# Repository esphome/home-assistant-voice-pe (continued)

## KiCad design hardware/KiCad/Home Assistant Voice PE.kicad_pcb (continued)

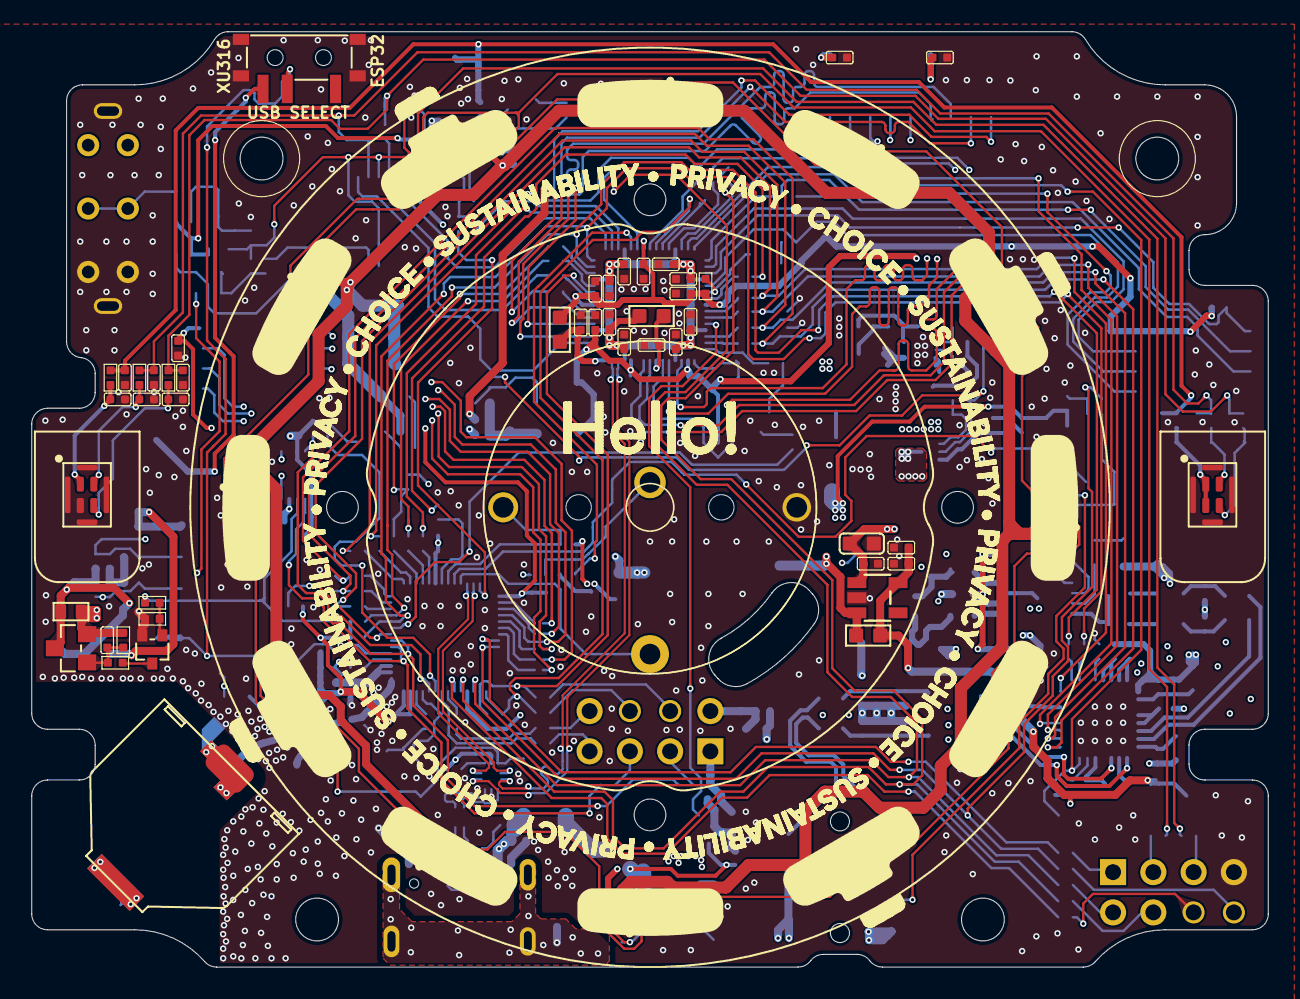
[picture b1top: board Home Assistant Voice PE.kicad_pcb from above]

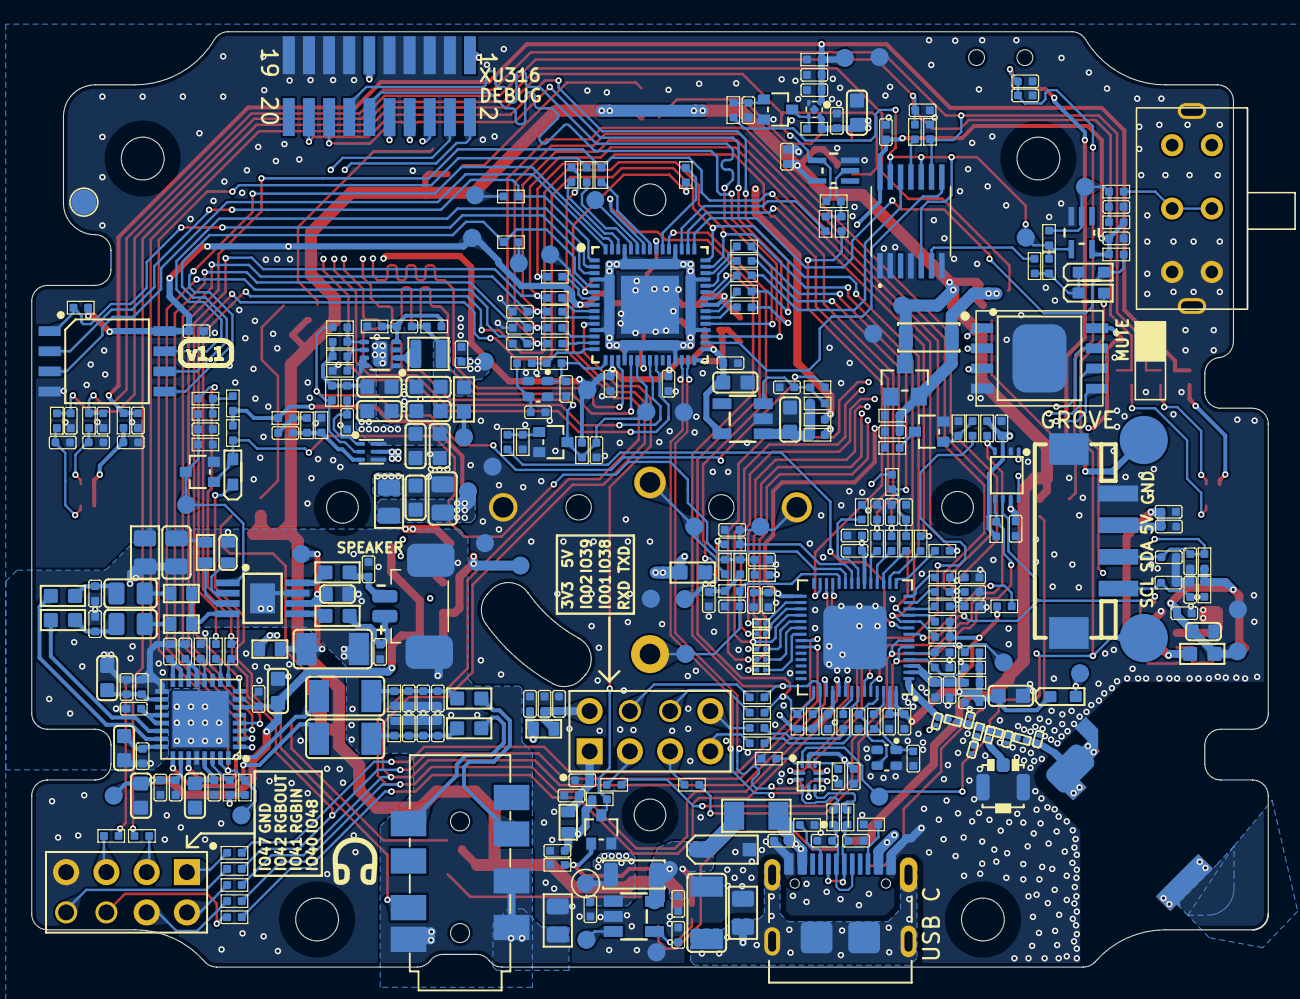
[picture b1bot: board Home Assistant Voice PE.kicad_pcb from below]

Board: 4 copper layers, 78.0 x 59.0 mm, 438 parts (365 on the bottom side), 239 nets.

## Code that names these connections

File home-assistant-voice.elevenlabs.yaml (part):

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
i2c:
  - id: internal_i2c
    sda: GPIO5
    scl: GPIO6
    frequency: 400kHz

psram:
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voice_kit:
  id: voice_kit_component
  i2c_id: internal_i2c
  reset_pin: GPIO4
  firmware:
    url: https://github.com/esphome/voice-kit-xmos-firmware/releases/download/v1.3.1/ffva_v1.3.1_upgrade.bin
    version: "1.3.1"
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i2s_audio:
  - id: i2s_output
    i2s_lrclk_pin:
      number: GPIO7
    i2s_bclk_pin:
      number: GPIO8

  - id: i2s_input
    i2s_lrclk_pin:
      number: GPIO14
    i2s_bclk_pin:
      number: GPIO13

microphone:
  - platform: i2s_audio
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    id: i2s_audio_speaker
    sample_rate: 48000
    i2s_mode: secondary
    i2s_dout_pin: GPIO10
    bits_per_sample: 32bit
    i2s_audio_id: i2s_output
    dac_type: external
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
power_supply:
  - id: led_power
    pin: GPIO45

select:
  - platform: template
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  - platform: gpio
    id: center_button
    pin:
      number: GPIO0
      inverted: true
    on_press:
      - script.execute: control_leds
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  - platform: gpio
    id: hardware_mute_switch
    internal: true
    pin: GPIO3
    on_press:
      # Play mute on sound only if software mute isn't enabled
      - if:
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      - delayed_on: 200ms
      - delayed_off: 200ms
    pin:
      number: GPIO17
    # When the jack is plugged in:
    #  - LED animation
    #  - Sound played
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  # Hardware LED ring. Not used because remapping needed
  - platform: esp32_rmt_led_strip
    id: leds_internal
    pin: GPIO21
    chipset: WS2812
    max_refresh_rate: 15ms
    num_leds: 12
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  - platform: rotary_encoder
    id: dial
    pin_a: GPIO16
    pin_b: GPIO18
    resolution: 2
    on_clockwise:
      - lambda: id(dial_touched) = true;
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
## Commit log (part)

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2024-10-17 move audio libraries to an external repo
2024-10-17 [nabu] move libraries to external repo (#167)
    * move audio libraries to an external repo
    * remove unnecessary imports
2024-10-19 Move setting global voice assistant to constructor (#168)
2024-10-21 Update voice_assistant.h (#169)
2024-10-21 Add beta install button (#171)
2024-10-21 Allow version to be specified and added as query param
2024-10-21 Allow version to be specified and added as query param (#173)
2024-10-21 [nabu] code cleanup with lint and clang fixes (#174)
2024-10-21 add more descriptive decoding errors
2024-10-21 [nabu] Improve error logging (#175)
    * reimplement flac decoder improvements
    * add more descriptive decoding errors
    * increase reader task stack size
    * remove unused variable
2024-10-21 add play local media file action
2024-10-21 [nabu] play local media file yaml action (#177)
    * add play local media file action
    * update todos
2024-10-22 Use remote paths for sounds (#178)
2024-10-22 Remove ACCESS POINT functionality (#179)
2024-10-24 use platformio library instead of repo
2024-10-24 [nabu] Use PlatformIO library instead of repo (#181)
    * use platformio library instead of repo
    * temporarily use branch
2024-10-24 reference dev branch (#182)
2025-02-19 use new audio output stack
2025-03-01 Expose Timer Events
2025-03-06 play preannounce media and enqueue the announcement
2025-03-06 only play preannounce url if non-empty
2025-03-20 build new firmware with ESPHome v2025.3.0
2025-03-24 set continue conversation boolean with start conversation flag
2025-03-25 bump build and min version to 2025.3.2
2025-03-27 Add Cloud Error Sound
2025-03-28 send "single_press" event
2025-03-31 bump to 25.3.3
2025-04-07 wake word stops ongoing VA session
2025-04-10 Better handle Stop word
2025-04-21 build with 2025.4.0
2025-04-30 Bump esphome/workflows from 2025.1.0 to 2025.4.0
    Bumps [esphome/workflows](https://github.com/esphome/workflows) from 2025.1.0 to 2025.4.0.
    - [Release notes](https://github.com/esphome/workflows/releases)
    - [Commits](https://github.com/esphome/workflows/compare/2025.1.0...2025.4.0)
    ---
    updated-dependencies:
    - dependency-name: esphome/workflows
2025-05-01 remove old external components - use the upstream versions
2025-05-02 don't use mic PR
2025-05-14 move read only and instructions from flash into psram on boot
2025-05-15 yamllint
2025-05-28 Modify default sensitivity
2025-06-26 Experimental PRs for testing, do not merge!
2025-06-29 bump build version and remove external components
2025-07-06 Switch to lock buttons
2025-07-14 feat: initial bridge
2025-07-14 fix: switch to testing via "run"
2025-07-14 fix: better test script
2025-07-14 fix: presigned url almost works
2025-07-15 fix: progress with HTTP reads
2025-07-15 fix: better elevenlabs compliance
2025-07-22 fix: more logging
2025-07-22 fix: switch to buffered approach
2025-07-22 fix: new test yaml
2025-07-22 fix: add resampler
2025-07-24 fix: compilation now works
2025-07-25 fix: type
2025-07-25 fix: cleanup later
2025-07-25 fix: reduce logging
2025-07-25 fix: elevenlabs conversation
2025-07-25 fix: better welcome message
2025-07-25 fix: better bitrate
2025-07-25 fix: higher performance
2025-07-26 fix: better activation sound
2025-07-26 fix: better documentation and better handling of speaker detection
2025-07-26 fix: implemented ring-buffer
2025-07-26 fix: buffer issue resolved
2025-07-26 fix: yaml should be OK
2025-07-26 fix: much better LED events
2025-07-26 fix: state bug
2025-07-26 fix: rename device name
2025-07-27 fix: remove voice kit
2025-07-27 fix: new parsing
2025-07-27 fix: compile issue
2025-07-27 fix: don't disable audio stream when wake word is detected during talking
2025-07-27 refactor: extract into separate classes
2025-07-27 fix: compile
2025-07-27 fix: signature.
2025-07-28 removes trailing space
2025-07-28 refactor: more cleanup
2025-07-28 refactor: base64 encoding is separate
2025-07-28 fix: compile error
2025-07-30 fix: jarvis no longer sounds like a chipmunk
2025-07-31 fix: work in progress for better speaker stability
2025-08-03 Added a configurable feature that uses the 'replying' led ring animation when playing externally triggered announcements. Enabled by default.
2025-08-12 Bump actions/checkout from 4.2.2 to 5.0.0
    Bumps [actions/checkout](https://github.com/actions/checkout) from 4.2.2 to 5.0.0.
    - [Release notes](https://github.com/actions/checkout/releases)
    - [Changelog](https://github.com/actions/checkout/blob/main/CHANGELOG.md)
    - [Commits](https://github.com/actions/checkout/compare/v4.2.2...v5.0.0)
    ---
    updated-dependencies:
2025-08-14 Add an option to processing audio file on thinking
2025-08-15 fix: stability improvements
2025-08-16 feat: add wake word sensitivity selector for Alexa
    FAPH on Dipco tests and values still missing
2025-08-25 Bump esphome/workflows from 2025.4.0 to 2025.8.1
    Bumps [esphome/workflows](https://github.com/esphome/workflows) from 2025.4.0 to 2025.8.1.
    - [Release notes](https://github.com/esphome/workflows/releases)
    - [Commits](https://github.com/esphome/workflows/compare/2025.4.0...2025.8.1)
    ---
    updated-dependencies:
    - dependency-name: esphome/workflows
2025-09-18 Bump actions/setup-python from 5 to 6
    Bumps [actions/setup-python](https://github.com/actions/setup-python) from 5 to 6.
    - [Release notes](https://github.com/actions/setup-python/releases)
    - [Commits](https://github.com/actions/setup-python/compare/v5...v6)
    ---
    updated-dependencies:
    - dependency-name: actions/setup-python
2025-10-01 Bump ESPHome to 2025.9.3
2025-10-02 Make some workflow strings more dynamic
2025-10-06 Bump esphome/workflows from 2025.8.1 to 2025.10.0
    Bumps [esphome/workflows](https://github.com/esphome/workflows) from 2025.8.1 to 2025.10.0.
    - [Release notes](https://github.com/esphome/workflows/releases)
    - [Commits](https://github.com/esphome/workflows/compare/2025.8.1...2025.10.0)
    ---
    updated-dependencies:
    - dependency-name: esphome/workflows
2025-11-01 adding support for openwakeword as a wake word engine. Adds a toggle in the home assistant integration section to switch between micro and openwakeword
2025-11-01 adding back comments and taking out more whitespace
2025-11-01 we love yaml
2025-11-19 Build with ESPHome 2025.11.0
2025-12-03 Bump actions/checkout from 5.0.0 to 6.0.1
    Bumps [actions/checkout](https://github.com/actions/checkout) from 5.0.0 to 6.0.1.
    - [Release notes](https://github.com/actions/checkout/releases)
    - [Changelog](https://github.com/actions/checkout/blob/main/CHANGELOG.md)
    - [Commits](https://github.com/actions/checkout/compare/v5.0.0...v6.0.1)
    ---
    updated-dependencies:
2025-12-17 Adds support for Sendspin
    - Use substitutions for all sound files
    - Replaces the speaker media player with a speaker source media player
    - Adds media sources for file, http, and Sendspin sources
    - Adds an internal only Sendspin media player to control an active group's volume (hold down the center button and spin the wheel)
    - Updates the play sound script and all calls to it to use the new URI based format for playing files
    - Updates all media player condtions and actions to specify an ID
2025-12-22 Use updated speaker source and sendspin components to request more sockets at build time
2025-12-24 update commit that uses different ctrl port to avoid conflict
2025-12-29 fix "stop" wake word not enabling for long TTS responses
2025-12-29 update commit that uses an int64 temporary to properly validate EAGAIN code
2026-01-19 Replace hey_jarvis model with listen_too_meeh
2026-01-21 Update wake word models in home-assistant-voice.yaml
    Removed 'okay_nabu' and 'hey_mycroft' models from configuration.
2026-01-21 bump to latest commits
2026-01-21 requires 2026.1.0 now for the OTA changes in the http component (that is pulled in by an external component)
2026-01-23 Bump actions/checkout from 6.0.1 to 6.0.2
    Bumps [actions/checkout](https://github.com/actions/checkout) from 6.0.1 to 6.0.2.
    - [Release notes](https://github.com/actions/checkout/releases)
    - [Changelog](https://github.com/actions/checkout/blob/main/CHANGELOG.md)
    - [Commits](https://github.com/actions/checkout/compare/v6.0.1...v6.0.2)
    ---
    updated-dependencies:
2026-01-23 Update external component URLs and models in YAML
2026-01-23 Fix formatting in home-assistant-voice.yaml
2026-01-23 Update model URLs and adjust sensitivity lambda
    my custom wake word
2026-02-12 use ESPHome dev branch commit hashes for merged mixer and resampler PRs (will be available in ESPHome 2026.2.0)
2026-02-12 Updates Sendspin commit hash
    - Implements a connection manager abstract class to handle multiple servers
    - Handles failed sent messages and no longer uses magic number delays on waiting for connections to close
    - Fixes potential overflow when adding/removing samples for soft syncs
    - Drastically reduces heap churn by using a once allocated ring buffer for encoded chunks and simplifies the syncing algorithm to avoid an std::deque
    - Improves the hub logic for starting a new stream to support the next MA beta that sends audio chunks much more rapidly
2026-02-12 Updates commit hash for media source media player
    - Fixes verify_ssl failing to work by using upstream http_request component
    - Fixes premature timeouts with slow TTS responses; now waits a full 30seconds before timing out compared to 4.5 seconds before
    - Includes stability fixes for the media source media player that should avoid getting in a stuck state causing watchdog timeouts
2026-02-12 use commit hash with MDNS code from 2026.1.5
2026-02-18 drop mixer and resampler external components; they are part of 2026.2.0
2026-02-18 bump min_version
2026-02-20 Move button action
2026-03-13 Add id to wake word sensitivity select
    `mww` already has an id, which can be used to extend the available wake words. This, however, will not have a settable sensitivity. Adding an `id` to the select will allow users to `!extend` the sele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
2026-03-23 Remove pinned mdns external component
    The mdns sendspin support from PR esphome/esphome#14013 was merged
    into ESPHome 2026.3.0, so the external component pin is no longer needed.
    The pinned mdns component references old code that declares
    `const std::string &friendly_name = App.get_friendly_name()`.
    Since ESPHome 2026.3.0, `get_friendly_name()` returns `const StringRef &`
    instead of `const std::string &`. This causes an implicit conversion
2026-03-23 use newer sha hash to reduce timeout warnings
2026-03-26 Bump actions/deploy-pages from 4.0.5 to 5.0.0
    Bumps [actions/deploy-pages](https://github.com/actions/deploy-pages) from 4.0.5 to 5.0.0.
    - [Release notes](https://github.com/actions/deploy-pages/releases)
    - [Commits](https://github.com/actions/deploy-pages/compare/v4.0.5...v5.0.0)
    ---
    updated-dependencies:
    - dependency-name: actions/deploy-pages
2026-04-15 Bump actions/github-script from 8.0.0 to 9.0.0
    Bumps [actions/github-script](https://github.com/actions/github-script) from 8.0.0 to 9.0.0.
    - [Release notes](https://github.com/actions/github-script/releases)
    - [Commits](https://github.com/actions/github-script/compare/v8.0.0...v9.0.0)
    ---
    updated-dependencies:
    - dependency-name: actions/github-script
2026-04-15 Bump esphome/workflows/.github/workflows/upload-to-gh-release.yml
    Bumps [esphome/workflows/.github/workflows/upload-to-gh-release.yml](https://github.com/esphome/workflows) from 2025.10.0 to 2026.4.0.
    - [Release notes](https://github.com/esphome/workflows/releases)
    - [Commits](https://github.com/esphome/workflows/compare/e7eee2a828517c042794a831f75310959fbf2a16...3c4e8446aa1029f1c346a482034b3ee1489077ca)
    ---
    updated-dependencies:
    - dependency-name: esphome/workflows/.github/workflows/upload-to-gh-release.yml
2026-04-15 Bump esphome/workflows/.github/workflows/upload-to-r2.yml
    Bumps [esphome/workflows/.github/workflows/upload-to-r2.yml](https://github.com/esphome/workflows) from 2025.10.0 to 2026.4.0.
    - [Release notes](https://github.com/esphome/workflows/releases)
    - [Commits](https://github.com/esphome/workflows/compare/e7eee2a828517c042794a831f75310959fbf2a16...3c4e8446aa1029f1c346a482034b3ee1489077ca)
    ---
    updated-dependencies:
    - dependency-name: esphome/workflows/.github/workflows/upload-to-r2.yml
2026-04-15 Fix dependabot pattern
2026-05-21 Build with 2026.5.0
2026-05-21 Bump the shared-workflows group with 4 updates
    Bumps the shared-workflows group with 4 updates: [esphome/workflows/.github/workflows/build.yml](https://github.com/esphome/workflows), [esphome/workflows/.github/workflows/upload-to-r2.yml](https://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
    Updates `esphome/workflows/.github/workflows/build.yml` from 2026.4.0 to 2026.4.1
    - [Release notes](https://github.com/esphome/workflows/releases)
    - [Commits](https://github.com/esphome/workflows/compare/3c4e8446aa1029f1c346
2026-05-25 Remove the second microphone channel from being sent to HA
    - Workaround for a bug where the `voice_assistant` component in 2026.5.0 can send an audio packet with zero length, which makes HA assume mic audio is done. This could potentially truncate commands.
2026-06-15 Support streaming wake word
